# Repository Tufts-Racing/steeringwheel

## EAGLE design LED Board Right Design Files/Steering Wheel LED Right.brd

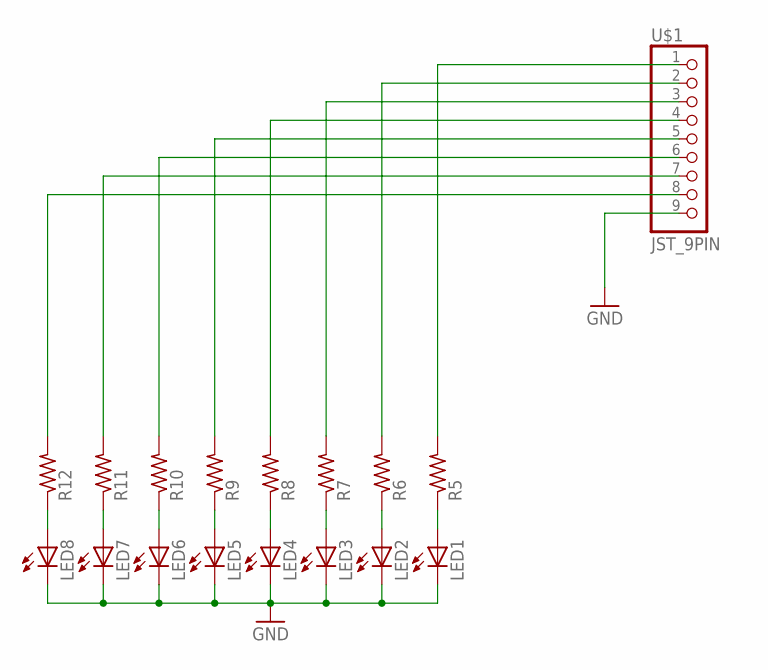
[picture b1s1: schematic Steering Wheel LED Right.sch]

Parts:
LED1, LED2, LED3, LED4, LED5, LED6, LED7, LED8: LED3MM
R5, R6, R7, R8, R9, R10, R11, R12: R-US_M1206; M1206
U$1: JST_9PIN; JST-PH-9-THM

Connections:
GND: LED1.K (C), LED2.K (C), LED3.K (C), LED4.K (C), LED5.K (C), LED6.K (C), LED7.K (C), LED8.K (C), U$1.9
unnamed: LED3.A, R7.1
unnamed: LED2.A, R6.1
unnamed: LED1.A, R5.1
unnamed: LED4.A, R8.1
unnamed: LED5.A, R9.1
unnamed: LED6.A, R10.1
unnamed: LED7.A, R11.1
unnamed: LED8.A, R12.1
unnamed: R10.2, U$1.6
unnamed: R5.2, U$1.1
unnamed: R6.2, U$1.2
unnamed: R7.2, U$1.3
unnamed: R8.2, U$1.4
unnamed: R9.2, U$1.5
unnamed: R11.2, U$1.7
unnamed: R12.2, U$1.8

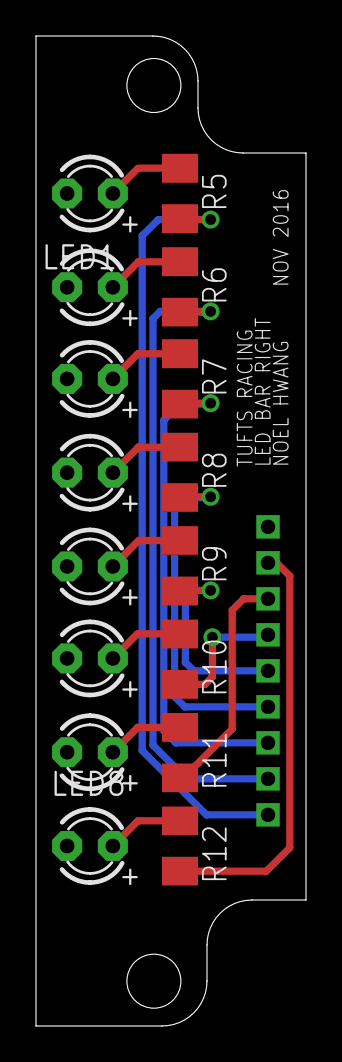
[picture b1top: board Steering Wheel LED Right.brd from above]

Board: 2 copper layers, 15.0 x 55.0 mm, 17 parts (1 on the bottom side), 17 nets.

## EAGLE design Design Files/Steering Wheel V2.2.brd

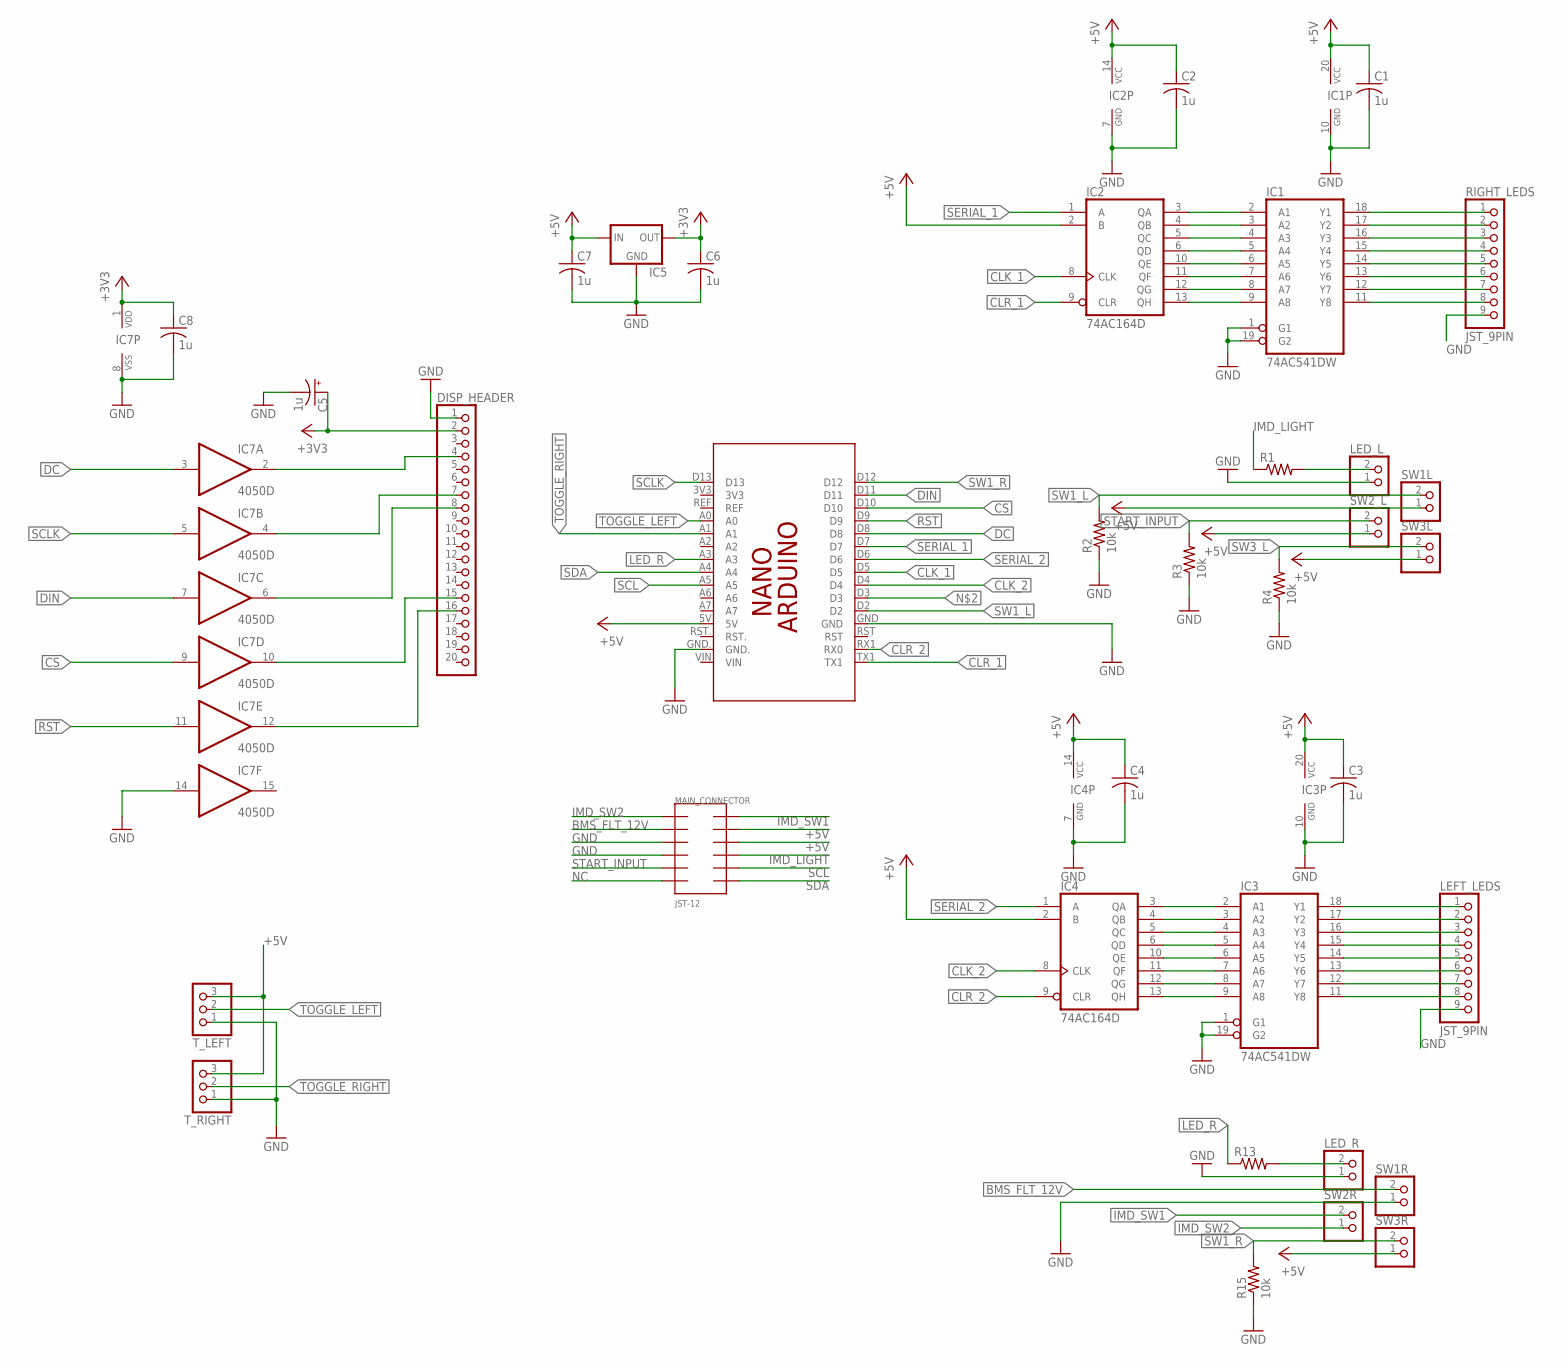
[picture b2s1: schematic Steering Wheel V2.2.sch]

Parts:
C1, C2, C3, C4, C6, C7, C8: 1u; C1206
C5: 1u; E3,5-8
DISP_HEADER: PINHD-1X20; 1X20
IC1, IC3: 74AC541DW; SO20W
IC2, IC4: 74AC164D; SO14
IC5: 78XXL
IC7: 4050D; SO16
LED_L: JST_2PIN-THM; JST-PH-2-THM
LED_R: JST_2PIN-THM; JST-PH-2-THM
LEFT_LEDS: JST_9PIN; JST-PH-9-THM
MAIN_CONNECTOR: JST-12; PHD-12
PCB1: ARDUINO_NANO
R1, R13: R-US_M1206; M1206
R2, R3, R4, R15: 10k; M1206
RIGHT_LEDS: JST_9PIN; JST-PH-9-THM
SW1L, SW1R, SW2R, SW2_L, SW3L, SW3R: JST_2PIN-THM; JST-PH-2-THM
T_LEFT: JST_3PIN; JST-PH-3-THM
T_RIGHT: JST_3PIN; JST-PH-3-THM

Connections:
+3V3: C5.+, C6.1, C8.1, DISP_HEADER.2, IC5.OUT, IC7.1 (VDD)
+5V: C1.1, C2.1, C3.1, C4.1, C7.1, IC1.20 (VCC), IC2.2 (B), IC2.14 (VCC), IC3.20 (VCC), IC4.2 (B), IC4.14 (VCC), IC5.IN, MAIN_CONNECTOR.10, MAIN_CONNECTOR.11, PCB1.5V, SW1L.1 (2), SW2_L.1 (2), SW3L.1 (2), SW3R.1 (2), T_LEFT.3, T_RIGHT.3
BMS_FLT_12V: MAIN_CONNECTOR.2, SW1R.2 (1)
CLK_1: IC2.8 (CLK), PCB1.D5
CLK_2: IC4.8 (CLK), PCB1.D4
CLR_1: IC2.9 (CLR), PCB1.TX1
CLR_2: IC4.9 (CLR), PCB1.RX1 (RX0)
CS: IC7.9 (I), PCB1.D10
DC: IC7.3 (I), PCB1.D8
DIN: IC7.7 (I), PCB1.D11
GND: C1.2, C2.2, C3.2, C4.2, C5.-, C6.2, C7.2, C8.2, DISP_HEADER.1, IC1.1 (G1), IC1.10 (GND), IC1.19 (G2), IC2.7 (GND), IC3.1 (G1), IC3.10 (GND), IC3.19 (G2), IC4.7 (GND), IC5.GND, IC7.8 (VSS), IC7.14 (I), LED_L.1 (2), LED_R.1 (2), LEFT_LEDS.9, MAIN_CONNECTOR.3, MAIN_CONNECTOR.4, PCB1.GND, PCB1.GND., R2.1, R3.1, R4.1, R15.1, RIGHT_LEDS.9, SW1R.1 (2), T_LEFT.1, T_RIGHT.1
IMD_LIGHT: MAIN_CONNECTOR.9, R1.1
IMD_SW1: MAIN_CONNECTOR.12, SW2R.2 (1)
IMD_SW2: MAIN_CONNECTOR.1, SW2R.1 (2)
LED_R: PCB1.A3, R13.1
LED_RIGHT: LED_R.2 (1), R13.2
unnamed: LED_L.2 (1), R1.2
unnamed: IC1.13 (Y6), RIGHT_LEDS.6
unnamed: IC1.15 (Y4), RIGHT_LEDS.4
unnamed: IC1.14 (Y5), RIGHT_LEDS.5
unnamed: IC1.12 (Y7), RIGHT_LEDS.7
unnamed: IC1.11 (Y8), RIGHT_LEDS.8
unnamed: IC1.9 (A8), IC2.13 (QH)
unnamed: IC1.2 (A1), IC2.3 (QA)
unnamed: IC1.3 (A2), IC2.4 (QB)
unnamed: IC1.4 (A3), IC2.5 (QC)
unnamed: IC1.5 (A4), IC2.6 (QD)
unnamed: IC1.6 (A5), IC2.10 (QE)
unnamed: IC1.7 (A6), IC2.11 (QF)
unnamed: IC1.8 (A7), IC2.12 (QG)
unnamed: IC3.18 (Y1), LEFT_LEDS.1
unnamed: IC3.17 (Y2), LEFT_LEDS.2
unnamed: IC3.16 (Y3), LEFT_LEDS.3
unnamed: IC3.15 (Y4), LEFT_LEDS.4
unnamed: IC3.14 (Y5), LEFT_LEDS.5
unnamed: IC3.13 (Y6), LEFT_LEDS.6
unnamed: IC3.12 (Y7), LEFT_LEDS.7
unnamed: IC3.11 (Y8), LEFT_LEDS.8
unnamed: IC3.9 (A8), IC4.13 (QH)
unnamed: IC3.2 (A1), IC4.3 (QA)
unnamed: IC3.3 (A2), IC4.4 (QB)
unnamed: IC3.4 (A3), IC4.5 (QC)
unnamed: IC3.5 (A4), IC4.6 (QD)
unnamed: IC3.6 (A5), IC4.10 (QE)
unnamed: IC3.7 (A6), IC4.11 (QF)
unnamed: IC3.8 (A7), IC4.12 (QG)
unnamed: DISP_HEADER.4, IC7.2 (O)
unnamed: DISP_HEADER.16, IC7.12 (O)
unnamed: DISP_HEADER.15, IC7.10 (O)
unnamed: IC1.18 (Y1), RIGHT_LEDS.1
unnamed: IC1.17 (Y2), RIGHT_LEDS.2
unnamed: IC1.16 (Y3), RIGHT_LEDS.3
unnamed: DISP_HEADER.7, IC7.4 (O)
unnamed: DISP_HEADER.8, IC7.6 (O)
NC: MAIN_CONNECTOR.6
RST: IC7.11 (I), PCB1.D9
SCL: MAIN_CONNECTOR.8, PCB1.A5
SCLK: IC7.5 (I), PCB1.D13
SDA: MAIN_CONNECTOR.7, PCB1.A4
SERIAL_1: IC2.1 (A), PCB1.D7
SERIAL_2: IC4.1 (A), PCB1.D6
START_INPUT: MAIN_CONNECTOR.5, R3.2, SW2_L.2 (1)
SW1_L: PCB1.D2, R2.2, SW1L.2 (1)
SW1_R: PCB1.D12, R15.2, SW3R.2 (1)
SW3_L: R4.2, SW3L.2 (1)
TOGGLE_LEFT: PCB1.A0, T_LEFT.2
TOGGLE_RIGHT: PCB1.A1, T_RIGHT.2

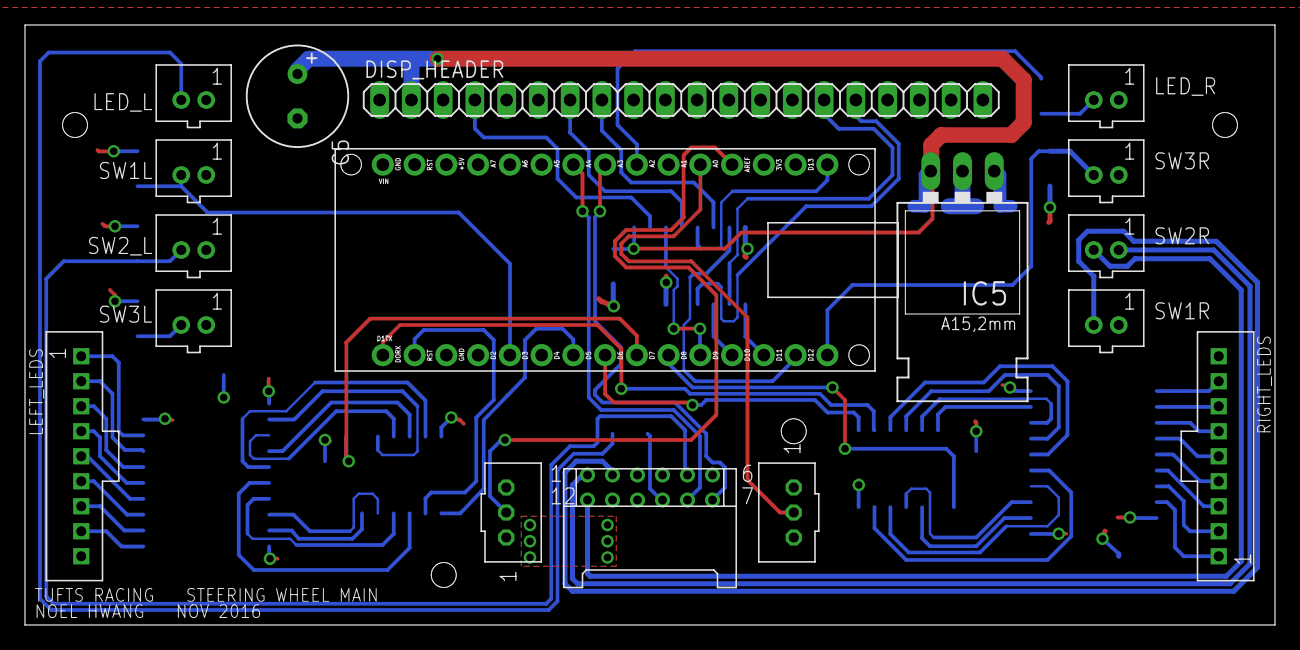
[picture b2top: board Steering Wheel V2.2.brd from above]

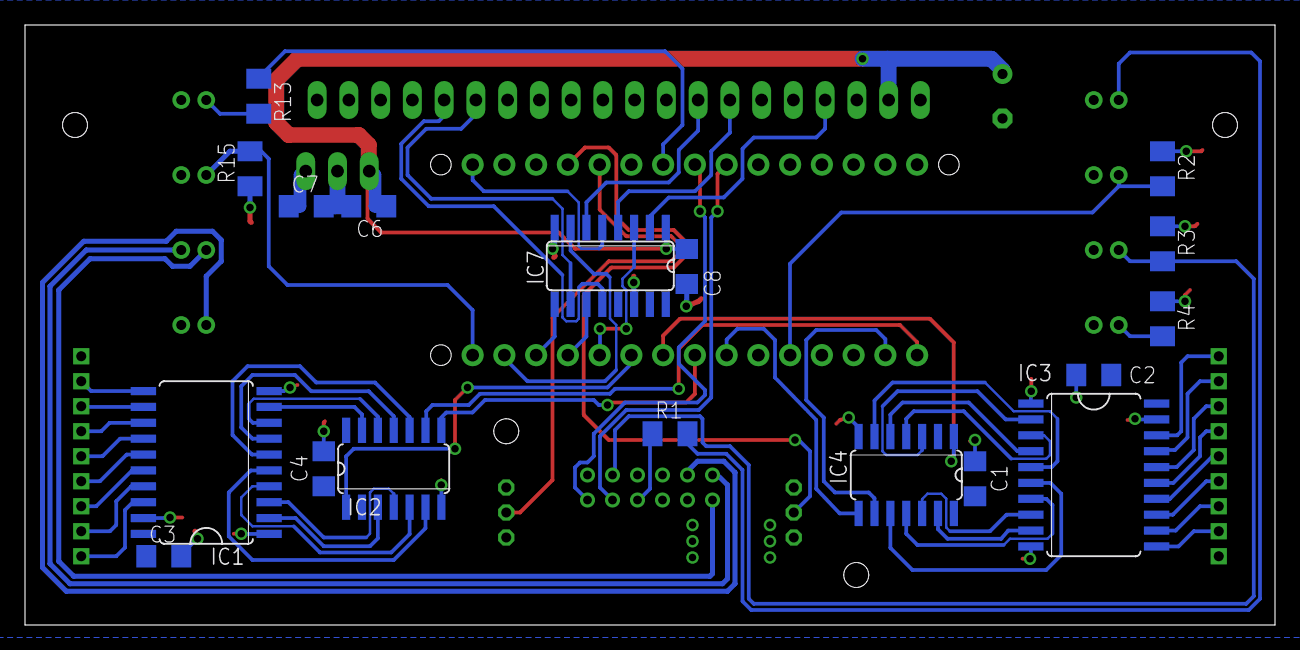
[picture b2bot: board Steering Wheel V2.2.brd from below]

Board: 2 copper layers, 100.0 x 48.0 mm, 35 parts (18 on the bottom side), 66 nets.

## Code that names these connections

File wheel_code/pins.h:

#ifndef PINS_H
#define PINS_H


// Display Pins
#define OLED_CLK 13
#define OLED_MOSI 11
#define OLED_CS 10
#define OLED_RESET 9
#define OLED_DC 8

// Buttons/Switches
#define SW1_L_IN 2
#define SW1_R_IN 12
#define FORWARD_IN A0
#define REVERSE_IN A2
#define DIR_PUSH_IN A6

//LEDs
#define LED_R A3

//Shift Registers
#define SERIAL_1 7
#define CLK_1 5
#define CLR_1 1

#define SERIAL_2 6
#define CLK_2 4
#define CLR_2 0

#define left 0
#define right 1

#endif

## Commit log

2017-03-01 :octocat: Added .gitattributes
2017-03-01 v1.0
2017-03-01 Add Design Files
2017-03-01 Added LED Design Files
2017-03-01 Added Passthrough
2017-03-05 Added Drivers and Libraries
2017-04-17 Two-action drive switch
2017-04-21 Direction Controls
2017-04-26 fixed IMD light
2017-05-01 fixed serial to mobo
2017-11-29 Began fixing extended compiler errors
    Changing defines to specified types
    Began making more readable
2017-11-29 Verbose Compiler Errors Fixed
    Fixed overflow error in toggle_disp_down
    Simplified toggle_disp_up
    Made switch_pos global and made enableDIR not redundant
    Added a number of TODOs
2017-12-06 Added Cockpit switch
    Added cockpit switch error read from wire
    Added cockpit switch output for errors
    Made error output only output a single error
2018-05-02 fixed drive direction changing
2019-02-11 SOLVED UNREPONSIVE CONTROLS
    Steering wheel was running out of RAM and could not keep up. Solved by
    commenting out all strings.
    TODO: determine if interrupt for enableDir() should be reimplemented,
    clean code
2019-02-11 Cleaned code a little
